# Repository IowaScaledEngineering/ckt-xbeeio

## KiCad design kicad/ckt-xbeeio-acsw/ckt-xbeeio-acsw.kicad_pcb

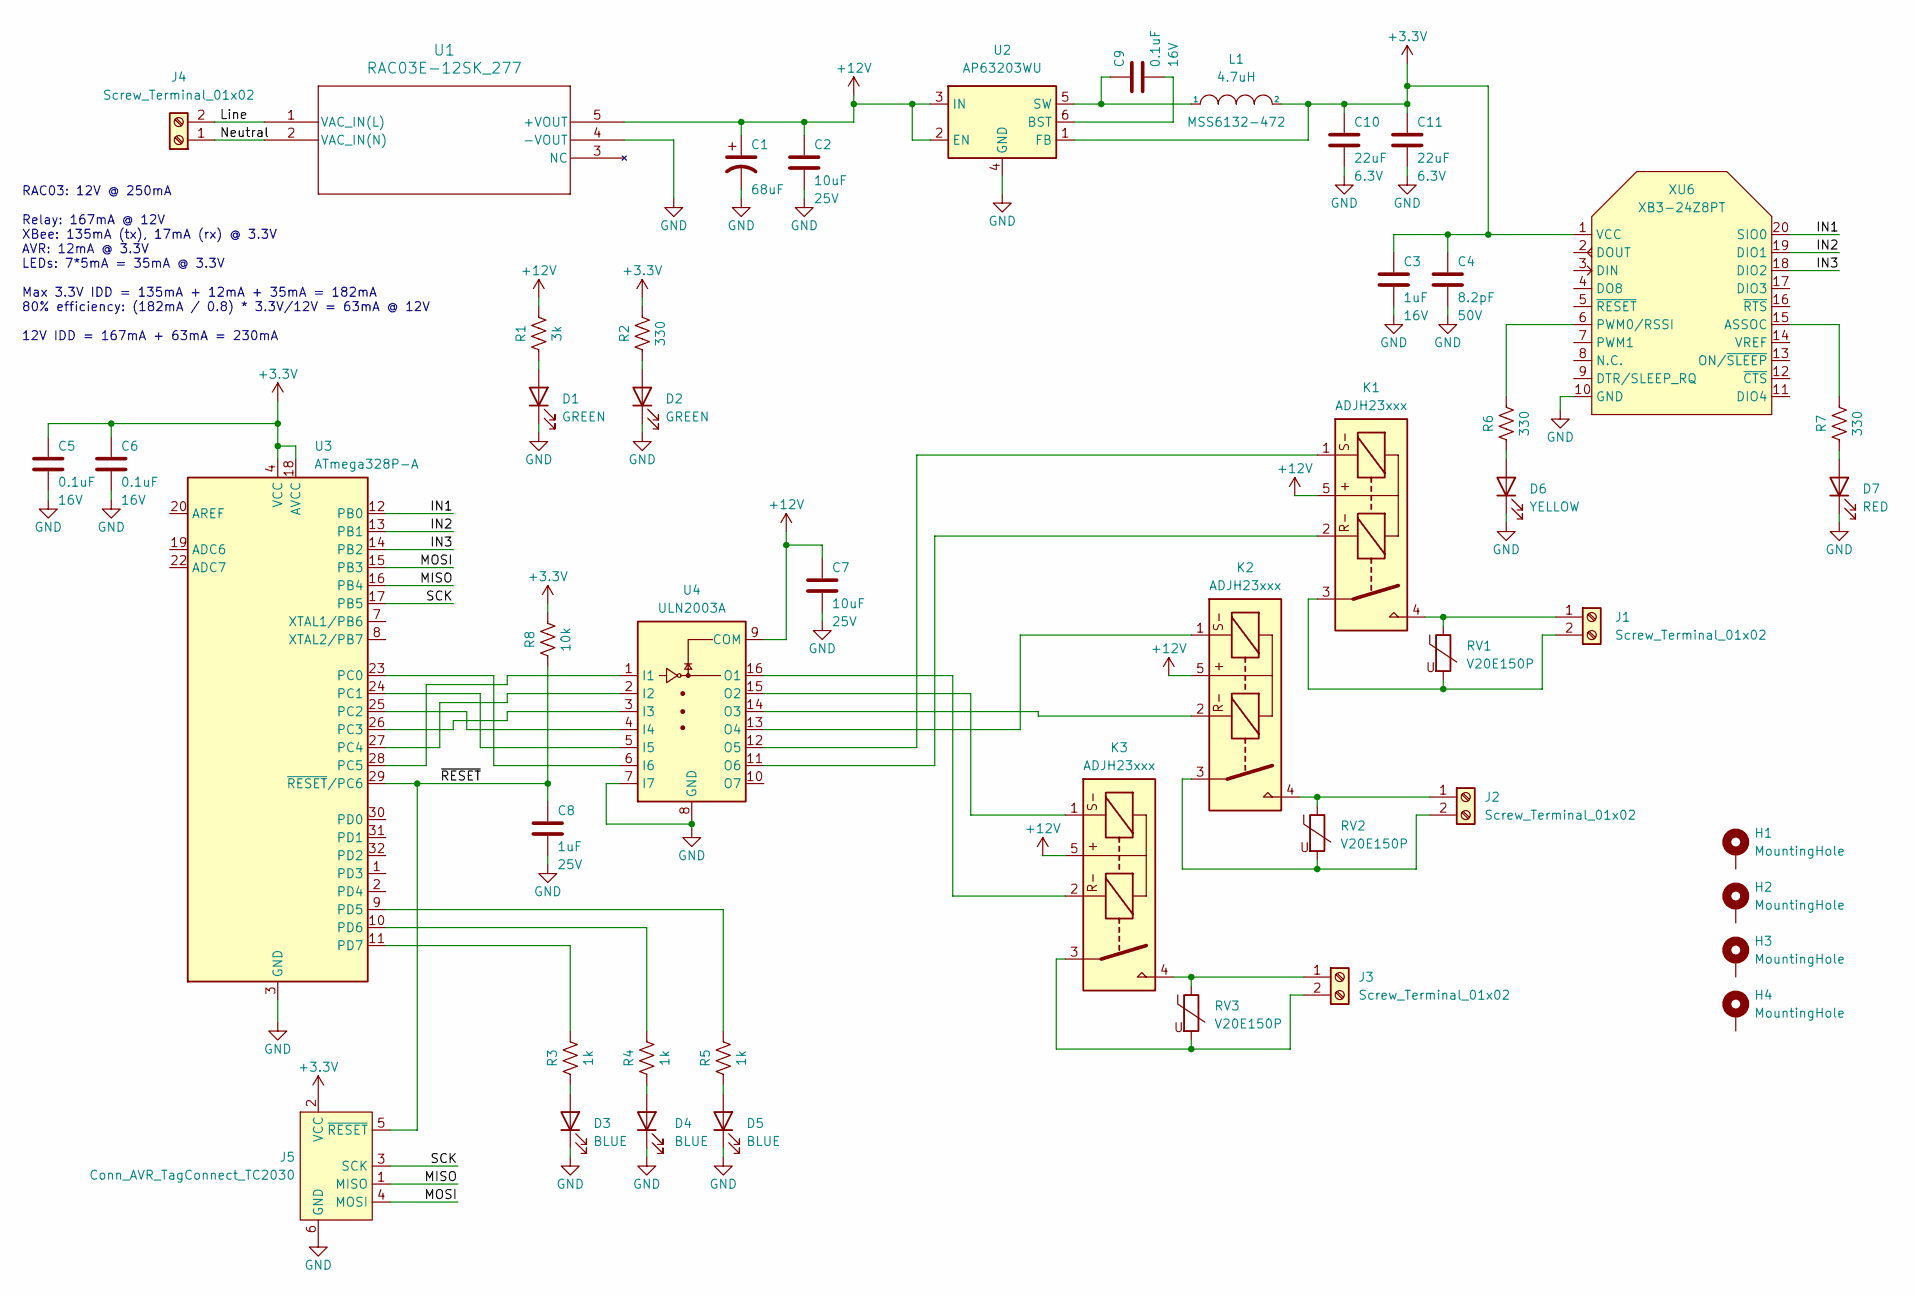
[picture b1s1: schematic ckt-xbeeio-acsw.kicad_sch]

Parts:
C1: 68uF; CP_Elec_6.3x5.8
C2, C7: 10uF; C_0805_2012Metric; Voltage 25V
C3: 1uF; C_0805_2012Metric; Voltage 16V
C4: 8.2pF; C_0805_2012Metric; Voltage 50V
C5, C6, C9: 0.1uF; C_0805_2012Metric; Voltage 16V
C8: 1uF; C_0805_2012Metric; Voltage 25V
C10, C11: 22uF; C_0805_2012Metric; Voltage 6.3V
D1, D2: GREEN; LED_0805_2012Metric
D3, D4, D5: BLUE; LED_0805_2012Metric
D6: YELLOW; LED_0805_2012Metric
D7: RED; LED_0805_2012Metric
H1, H2, H3, H4: MountingHole; MountingHole_3.2mm_M3_Pad
J1, J2, J3, J4: Screw_Terminal_01x02; CONN_1714971_PXC
J5: Conn_AVR_TagConnect_TC2030; Tag-Connect_TC2030-IDC-NL_2x03_P1.27mm_Vertical
K1, K2, K3: ADJH23xxx; ADJH2xxxx
L1: 4.7uH; MSS6132-xxxMLC
R1: 3k; R_0805_2012Metric
R2, R6, R7: 330; R_0805_2012Metric
R3, R4, R5: 1k; R_0805_2012Metric
R8: 10k; R_0805_2012Metric
RV1, RV2, RV3: V20E150P; RV_Disc_D21.5mm_W4.3mm_P10mm
U1: RAC03E-12SK_277; RAC03E-K_277_RCP
U2: AP63203WU; TSOT-23-6
U3: ATmega328P-A; TQFP-32_7x7mm_P0.8mm
U4: ULN2003A; SO-16_3.9x9.9mm_P1.27mm
XU6: XB3-24Z8PT; XBEE-SMD

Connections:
+3.3V: C3.1, C4.1, C5.1, C6.1, C10.1, C11.1, J5.2 (VCC), L1.2, R2.2, R8.2, U2.1 (FB), U3.4 (VCC), U3.6 (VCC), U3.18 (AVCC), XU6.1 (VCC)
+12V: C1.1, C2.1, C7.1, K1.5, K2.5, K3.5, R1.2, U1.5 (+VOUT), U2.2 (EN), U2.3 (IN), U4.9 (COM)
/IN1: U3.12 (PB0), XU6.20 (SIO0)
/IN2: U3.13 (PB1), XU6.19 (DIO1)
/IN3: U3.14 (PB2), XU6.18 (DIO2)
/Line: J4.2, U1.1 (VAC_IN(L))
/MISO: J5.1 (MISO), U3.16 (PB4)
/MOSI: J5.4 (MOSI), U3.15 (PB3)
/Neutral: J4.1, U1.2 (VAC_IN(N))
/SCK: J5.3 (SCK), U3.17 (PB5)
/~RESET: C8.1, J5.5 (~RESET), R8.1, U3.29 (~RESET/PC6)
GND: C1.2, C2.2, C3.2, C4.2, C5.2, C6.2, C7.2, C8.2, C10.2, C11.2, D1.1 (K), D2.1 (K), D3.1 (K), D4.1 (K), D5.1 (K), D6.1 (K), D7.1 (K), J5.6 (GND), U1.4 (-VOUT), U2.4 (GND), U3.3 (GND), U3.5 (GND), U3.21 (GND), U4.7 (I7), U4.8 (GND), XU6.10 (GND)
unnamed: C9.1, L1.1, U2.5 (SW)
unnamed: C9.2, U2.6 (BST)
unnamed: D1.2 (A), R1.1
unnamed: D2.2 (A), R2.1
unnamed: D3.2 (A), R3.1
unnamed: D4.2 (A), R4.1
unnamed: D5.2 (A), R5.1
unnamed: D6.2 (A), R6.1
unnamed: D7.2 (A), R7.1
unnamed: J1.1, K1.4, RV1.1
unnamed: J1.2, K1.3, RV1.2
unnamed: J2.1, K2.4, RV2.1
unnamed: J2.2, K2.3, RV2.2
unnamed: J3.1, K3.4, RV3.1
unnamed: J3.2, K3.3, RV3.2
unnamed: K1.1, U4.12 (O5)
unnamed: K1.2, U4.11 (O6)
unnamed: K2.1, U4.13 (O4)
unnamed: K2.2, U4.14 (O3)
unnamed: K3.1, U4.15 (O2)
unnamed: K3.2, U4.16 (O1)
unnamed: R3.2, U3.11 (PD7)
unnamed: R4.2, U3.10 (PD6)
unnamed: R5.2, U3.9 (PD5)
unnamed: R6.2, XU6.6 (PWM0/RSSI)
unnamed: R7.2, XU6.15 (ASSOC)
unnamed: U3.23 (PC0), U4.6 (I6)
unnamed: U3.24 (PC1), U4.5 (I5)
unnamed: U3.25 (PC2), U4.4 (I4)
unnamed: U3.26 (PC3), U4.3 (I3)
unnamed: U3.27 (PC4), U4.2 (I2)
unnamed: U3.28 (PC5), U4.1 (I1)

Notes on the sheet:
RAC03: 12V @ 250mA Relay: 167mA @ 12V XBee: 135mA (tx), 17mA (rx) @ 3.3V AVR: 12mA @ 3.3V LEDs: 7*5mA = 35mA @ 3.3V Max 3.3V IDD = 135mA + 12mA + 35mA = 182mA 80% efficiency: (182mA / 0.8) * 3.3V/12V = 63mA @ 12V 12V IDD = 167mA + 63mA = 230mA

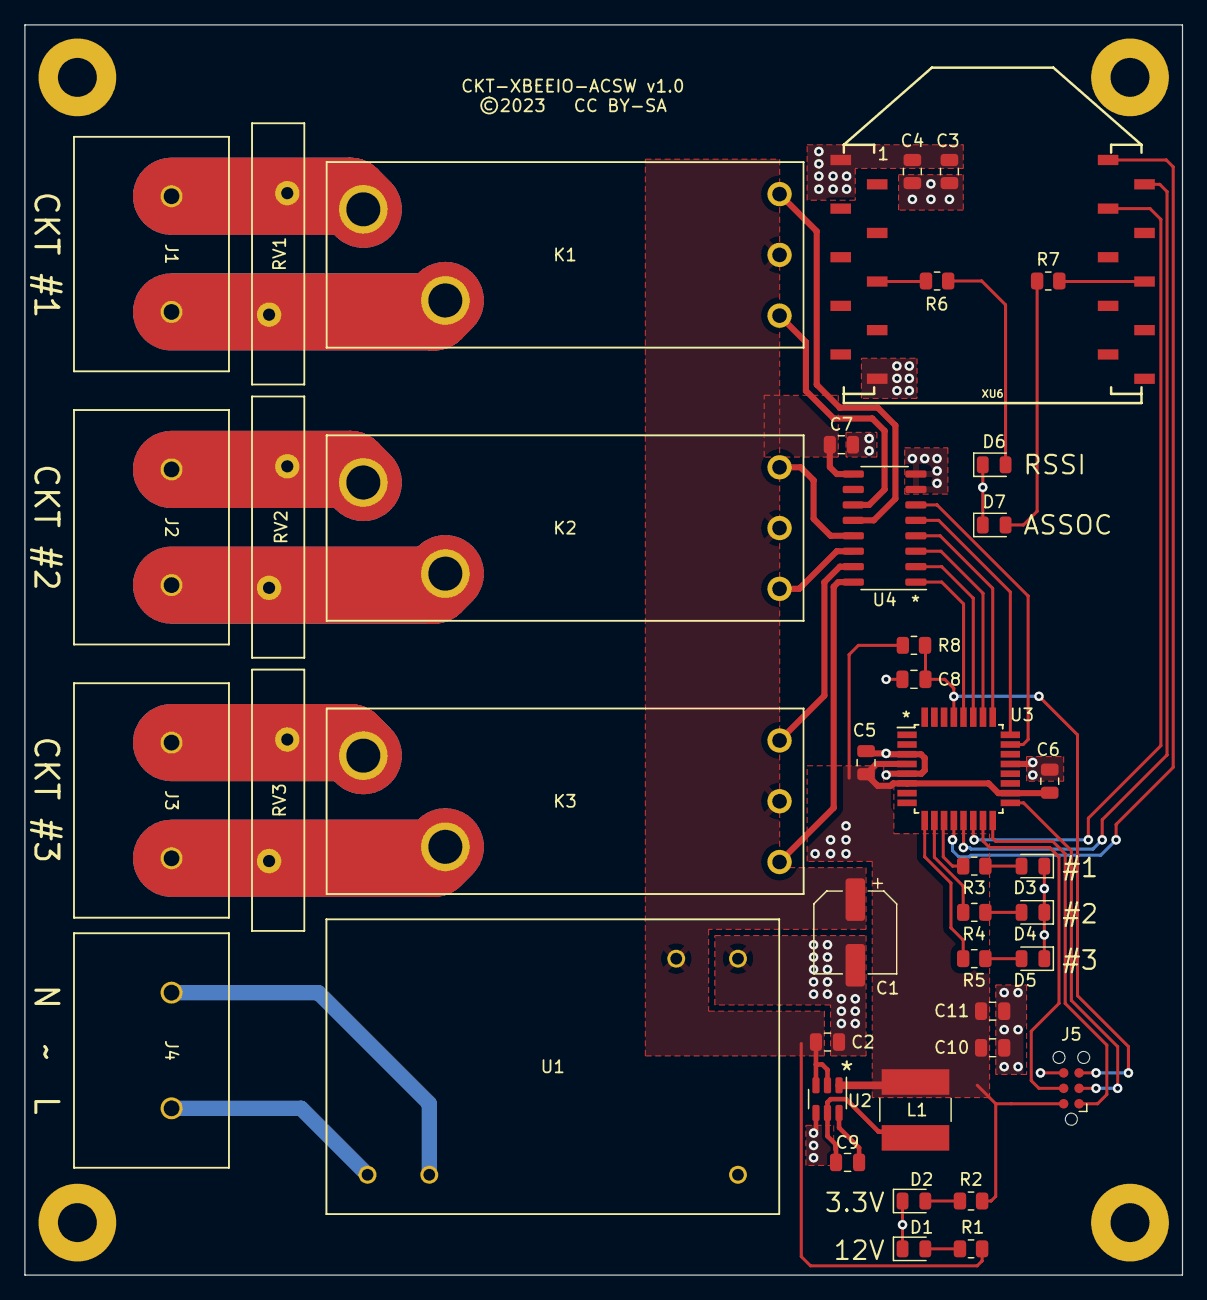
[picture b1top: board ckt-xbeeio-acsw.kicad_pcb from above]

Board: 2 copper layers, 95.2 x 102.9 mm, 47 parts (0 on the bottom side), 44 nets.

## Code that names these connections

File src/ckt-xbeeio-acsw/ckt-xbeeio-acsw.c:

/*************************************************************************
Title:    XBee based AC switch
Authors:  Michael Petersen <railfan@drgw.net>
File:     CKT-XBEEIO-ACSW
License:  GNU General Public License v3

LICENSE:
    Copyright (C) 2024 Michael Petersen

    This program is free software; you can redistribute it and/or modify
    it under the terms of the GNU General Public License as published by
    the Free Software Foundation; either version 2 of the License, or
    any later version.

    This program is distributed in the hope that it will be useful,
    but WITHOUT ANY WARRANTY; without even the implied warranty of
    MERCHANTABILITY or FITNESS FOR A PARTICULAR PURPOSE.  See the
    GNU General Public License for more details.

*************************************************************************/

#include <stdlib.h>
#include <avr/io.h>
#include <avr/wdt.h>
#include <util/delay.h>

uint8_t readInput(uint8_t input)
{
	uint8_t inputPin;
	switch(input)
	{
		case 0:
			inputPin = PB0;
			break;
		case 1:
			inputPin = PB1;
			break;
		case 2:
			inputPin = PB2;
			break;
		default:
			return 0;
	}
	return(PINB & _BV(inputPin));
}

void setLed(uint8_t led, uint8_t val)
{
	if(led > 2)
		return;
	if(val)
		PORTD |= _BV(7-led);
	else
		PORTD &= ~(_BV(7-led));
}

void setRelay(uint8_t relay, uint8_t val)
{
	uint8_t setPin, resetPin;
	switch(relay)
	{
		case 0:
			setPin = PC1;
			resetPin = PC0;
			break;
		case 1:
			setPin = PC2;
			resetPin = PC3;
			break;
		case 2:
			setPin = PC4;
			resetPin = PC5;
			break;
		default:
			return;
	}
	if(val)
	{
		setLed(relay,1);
		PORTC |= _BV(setPin);
		wdt_reset();
		_delay_ms(150);
		PORTC &= ~(_BV(setPin));
	}
	else
	{
		setLed(relay,0);
		PORTC |= _BV(resetPin);
		wdt_reset();
		_delay_ms(150);
		PORTC &= ~(_BV(resetPin));
	}
}

void init(void)
{
	// Kill watchdog
	MCUSR = 0;

	wdt_reset();
	WDTCSR |= _BV(WDE) | _BV(WDCE);
	WDTCSR = _BV(WDE) | _BV(WDP2) | _BV(WDP1); // Set the WDT to system reset and 1s timeout
	wdt_reset();

	PORTC = 0;
	DDRC = _BV(PD0) | _BV(PD1) | _BV(PD2) | _BV(PD3) | _BV(PD4) | _BV(PD5);
	PORTD = 0;
	DDRD = _BV(PD5) | _BV(PD6) | _BV(PD7);
}

int main(void)
{
	uint8_t oldVal[3] = {0, 0, 0};
	uint8_t i;
	uint8_t val;
	// Application initialization
	init();

	// Do something at startup and also give the XBee time to receive data from the switch
	wdt_reset();
	_delay_ms(750);

	setLed(0,1);
	wdt_reset();
	_delay_ms(500);
	setLed(0,0);

	setLed(1,1);
	wdt_reset();
	_delay_ms(500);
	setLed(1,0);

	setLed(2,1);
	wdt_reset();
	_delay_ms(500);
	setLed(2,0);

	setLed(0,1);
	setLed(1,1);
	setLed(2,1);
	wdt_reset();
	_delay_ms(750);
	setLed(0,0);
	setLed(1,0);
	setLed(2,0);

	wdt_reset();
	_delay_ms(500);
	wdt_reset();

	// Read input pins and pre-configure relays to match
	for(i=0; i<3; i++)
	{
		wdt_reset();
		oldVal[i] = readInput(i);
		setRelay(i, oldVal[i]);
	}

	while (1)
	{
		for(i=0; i<3; i++)
		{
			wdt_reset();
			val = readInput(i);
			if(val != oldVal[i])
			{
				setRelay(i, val);
				oldVal[i] = val;
			}
		}
	}
}

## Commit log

2022-05-14 Added LED polarity markers
2022-05-15 Sent to fab 5/14/2022
2023-09-03 Initial checkin of ckt-xbeeio-acsw
2023-09-04 Layout completed
2023-09-04 Improved metalization, added text
2023-09-04 Small improvements
2023-09-06 Changed soldermask clearance to 3mil
2023-09-06 Added pin 1 markers
2023-09-17 Changed to 8/8 rules
2023-09-21 Sent to fab Sep 2023
2024-05-06 Initial code
2024-05-06 Removed interrupts and other extraneous code
2024-05-06 Added size target

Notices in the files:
kicad/ckt-xbeeio-acsw/ckt-xbeeio-acsw.kicad_pcb:
©2023 CC BY-SA
